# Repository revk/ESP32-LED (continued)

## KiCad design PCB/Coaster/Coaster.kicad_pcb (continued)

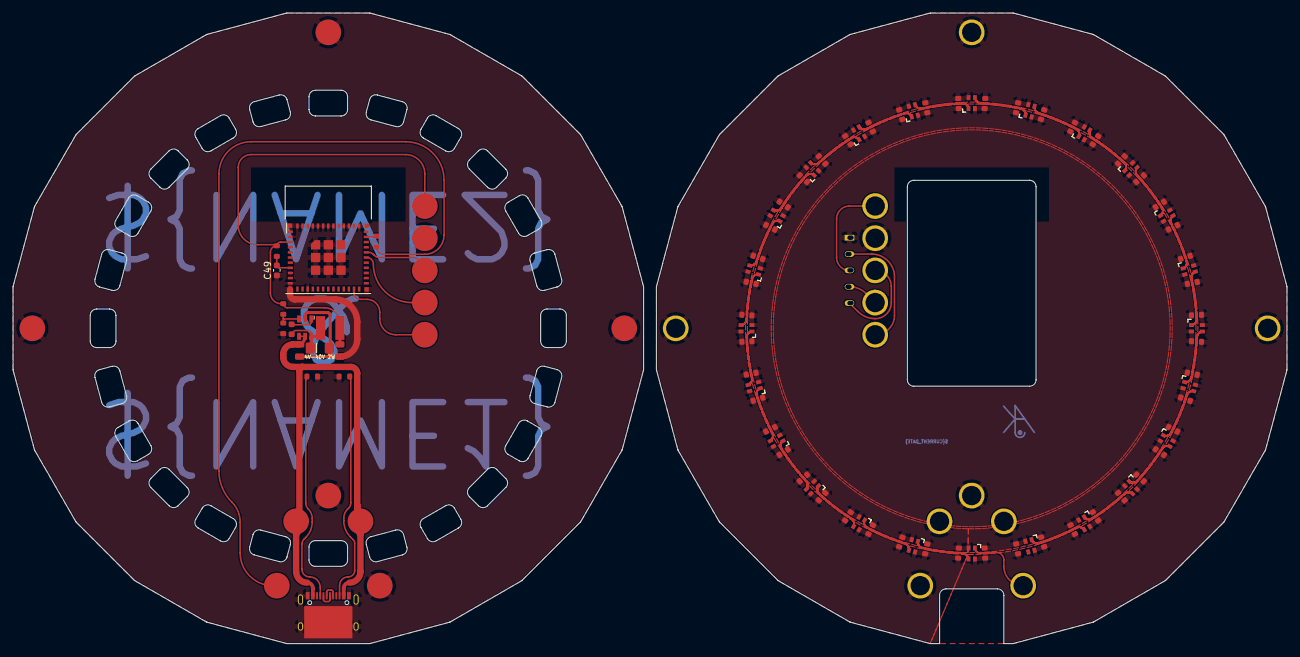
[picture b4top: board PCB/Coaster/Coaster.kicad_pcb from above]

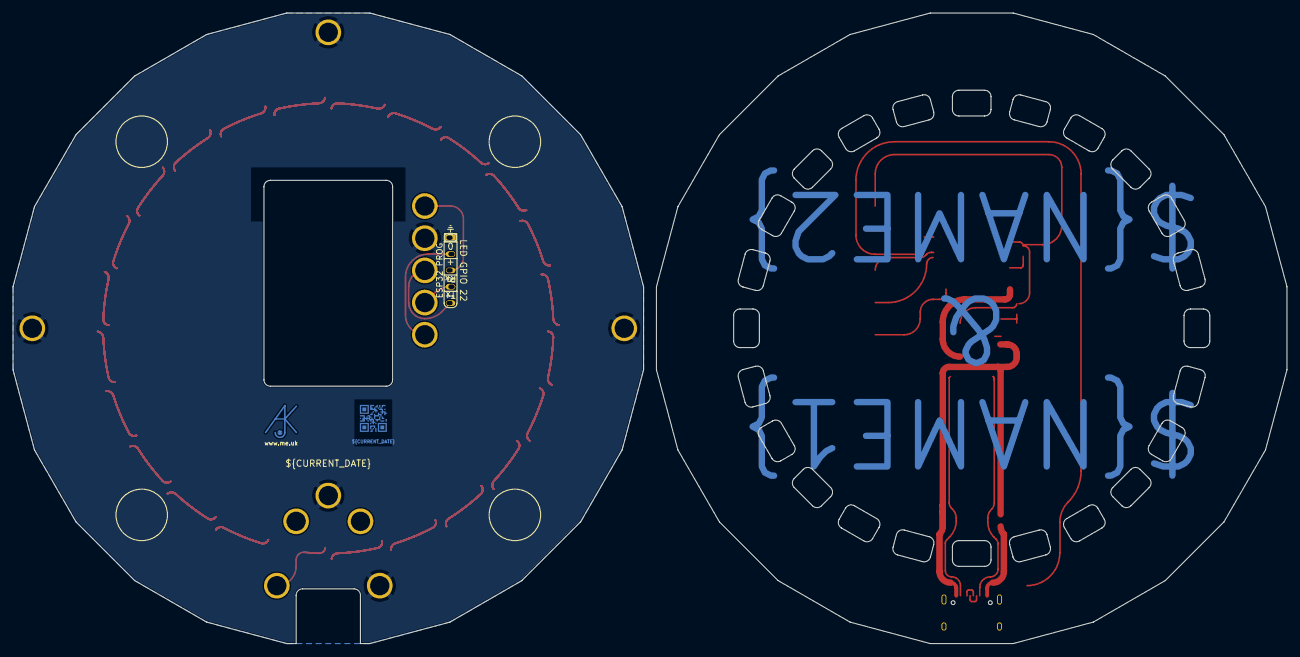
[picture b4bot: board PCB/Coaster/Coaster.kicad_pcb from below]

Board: 11 copper layers, 198.0 x 98.0 mm, 140 parts (3 on the bottom side), 42 nets.

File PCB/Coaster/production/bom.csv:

Designator,Footprint,Quantity,Value,LCSC Part #
"C1, C10, C11, C12, C13, C14, C15, C16, C17, C18, C19, C2, C20, C21, C22, C23, C24, C25, C26, C27, C28, C29, C3, C30, C31, C32, C33, C34, C35, C36, C37, C38, C39, C4, C40, C41, C42, C43, C44, C45, C46, C47, C48, C5, C6, C7, C8, C9",C_0603,48,100nF,
C49,0603,1,10nF,
C50,C_0603_,1,100nF,C30926
C51,C_0805_,1,2.2uF,C19110
C52,C_0805_,1,10uF,C17024
"D1, D10, D11, D12, D13, D14, D15, D16, D17, D18, D19, D2, D20, D21, D22, D23, D24, D3, D4, D5, D6, D7, D8, D9",SMD2020,24,WS2812B-2mm,C784564
D25,D_1206_,1,Schottky,C143805
J1,USC16-TR,1,USB-C,C709357
L1,L_4x4_,1,6.8uH,C354575
R1,R_0603,1,10k,
"R2, R3",R_0603,2,5K1,
R4,R_0603,1,300R,
R5,R_0603,1,100k 1%,C14675
R6,R_0603,1,30k 1%,C100001
U1,ESP32-PICO-MINI-02,1,ESP32-PICO-MINI-02,C2980306
U2,SOT-23-Thin-6-Reg,1,LMR16006XDDCR,C87080
